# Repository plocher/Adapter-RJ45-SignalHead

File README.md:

# Adapter-RJ45-SignalHead
## License: CERN Open Hardware Licence v1.2

RJ45/8 breakout board, for driving signal heads from IOB-Signal

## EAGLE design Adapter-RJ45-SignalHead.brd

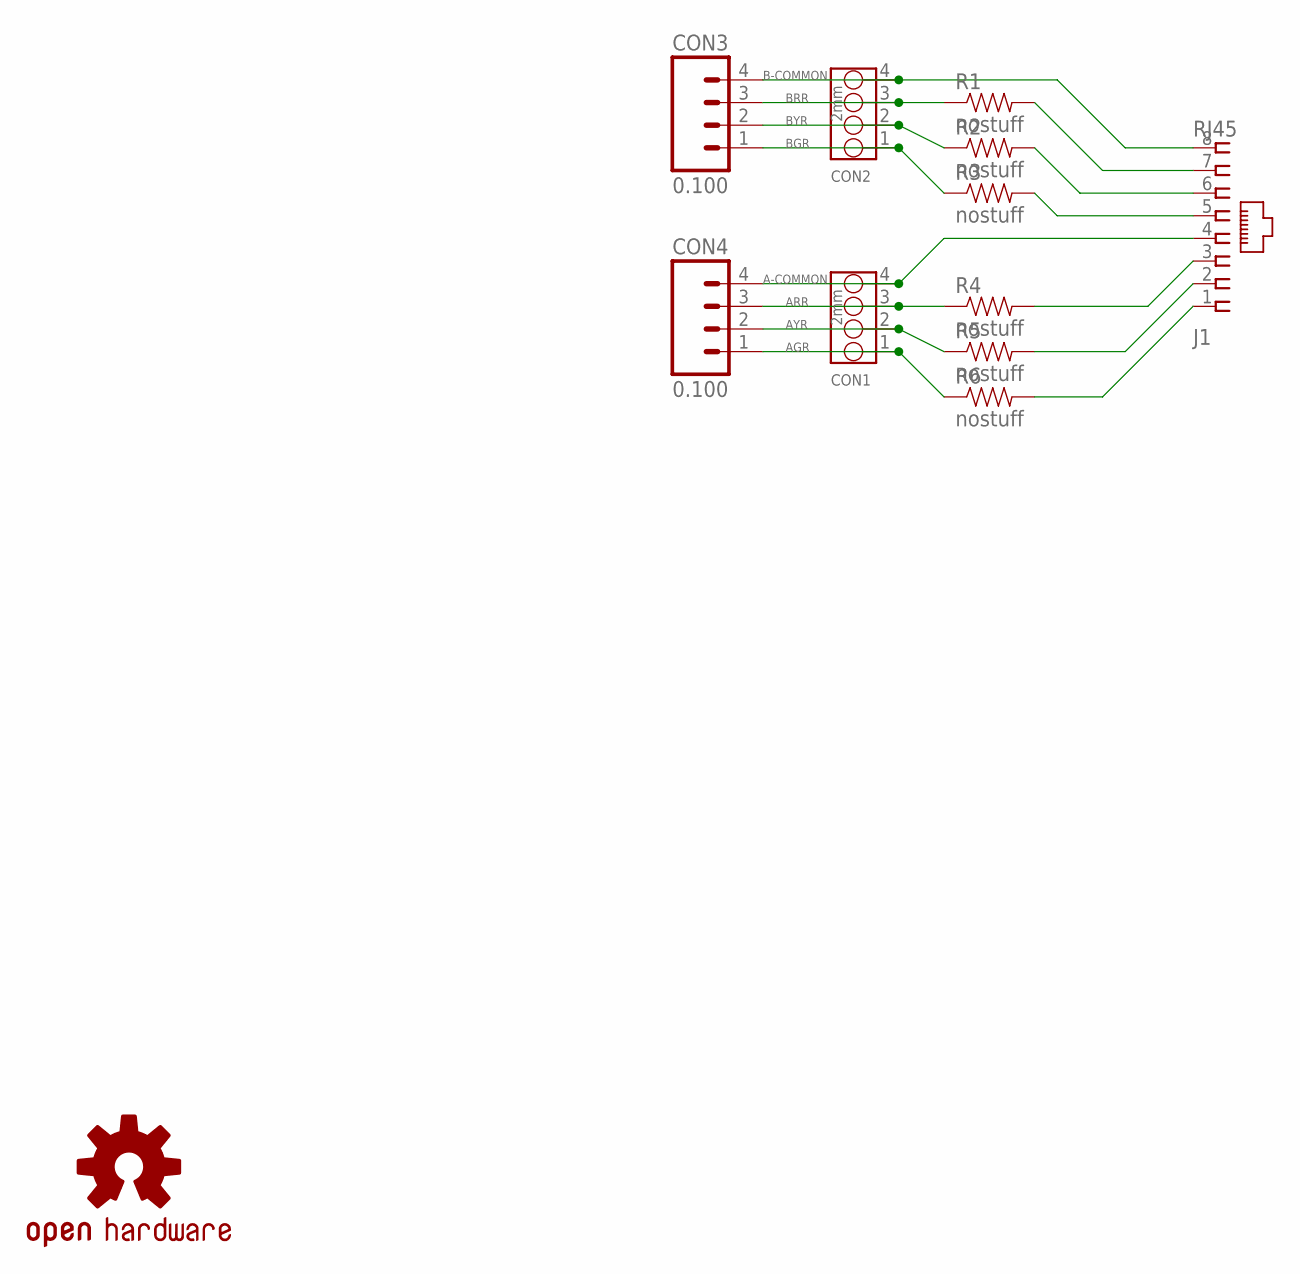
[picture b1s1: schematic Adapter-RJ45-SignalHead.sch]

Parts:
CON1, CON2: 2mm; 4P-2.0
CON3, CON4: 0.100; 1X04_LOCK
J1: RJ45; RJ45-NO-SHIELD
R1, R2, R3, R4, R5, R6: nostuff; CUT-R
U$1: OSHW; OSHW-LOGO-M

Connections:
A-COMMON: CON1.4, CON4.4, J1.4
AG: J1.1, R6.P1 (2)
AGR: CON1.1, CON4.1, R6.P2 (1)
AR: J1.3, R4.P1 (2)
ARR: CON1.3, CON4.3, R4.P2 (1)
AY: J1.2, R5.P1 (2)
AYR: CON1.2, CON4.2, R5.P2 (1)
B-COMMON: CON2.4, CON3.4, J1.8
BG: J1.5, R3.P1 (2)
BGR: CON2.1, CON3.1, R3.P2 (1)
BR: J1.7, R1.P1 (2)
BRR: CON2.3, CON3.3, R1.P2 (1)
BY: J1.6, R2.P1 (2)
BYR: CON2.2, CON3.2, R2.P2 (1)

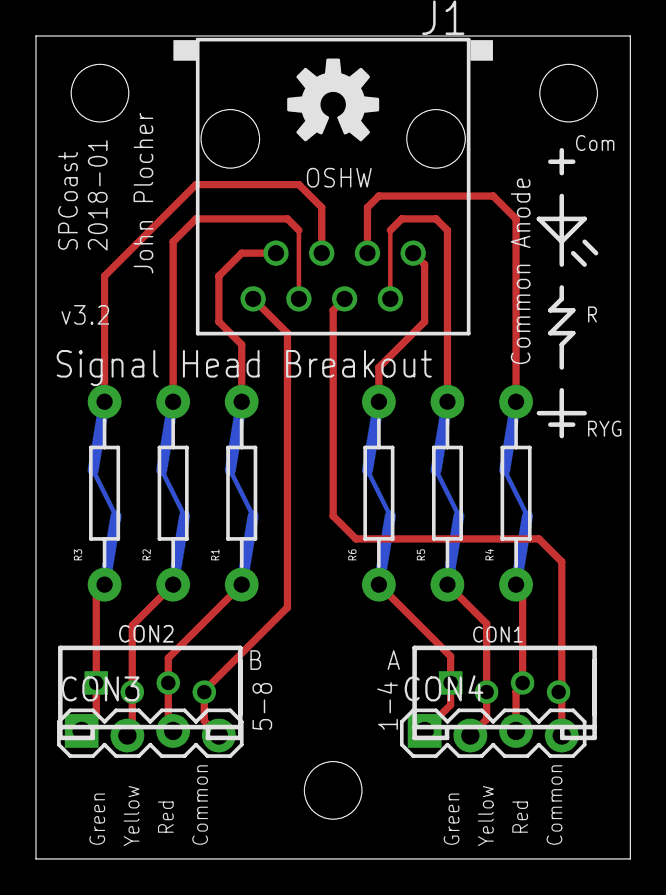
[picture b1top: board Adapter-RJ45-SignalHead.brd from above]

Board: 2 copper layers, 33.0 x 45.7 mm, 12 parts (0 on the bottom side), 14 nets.

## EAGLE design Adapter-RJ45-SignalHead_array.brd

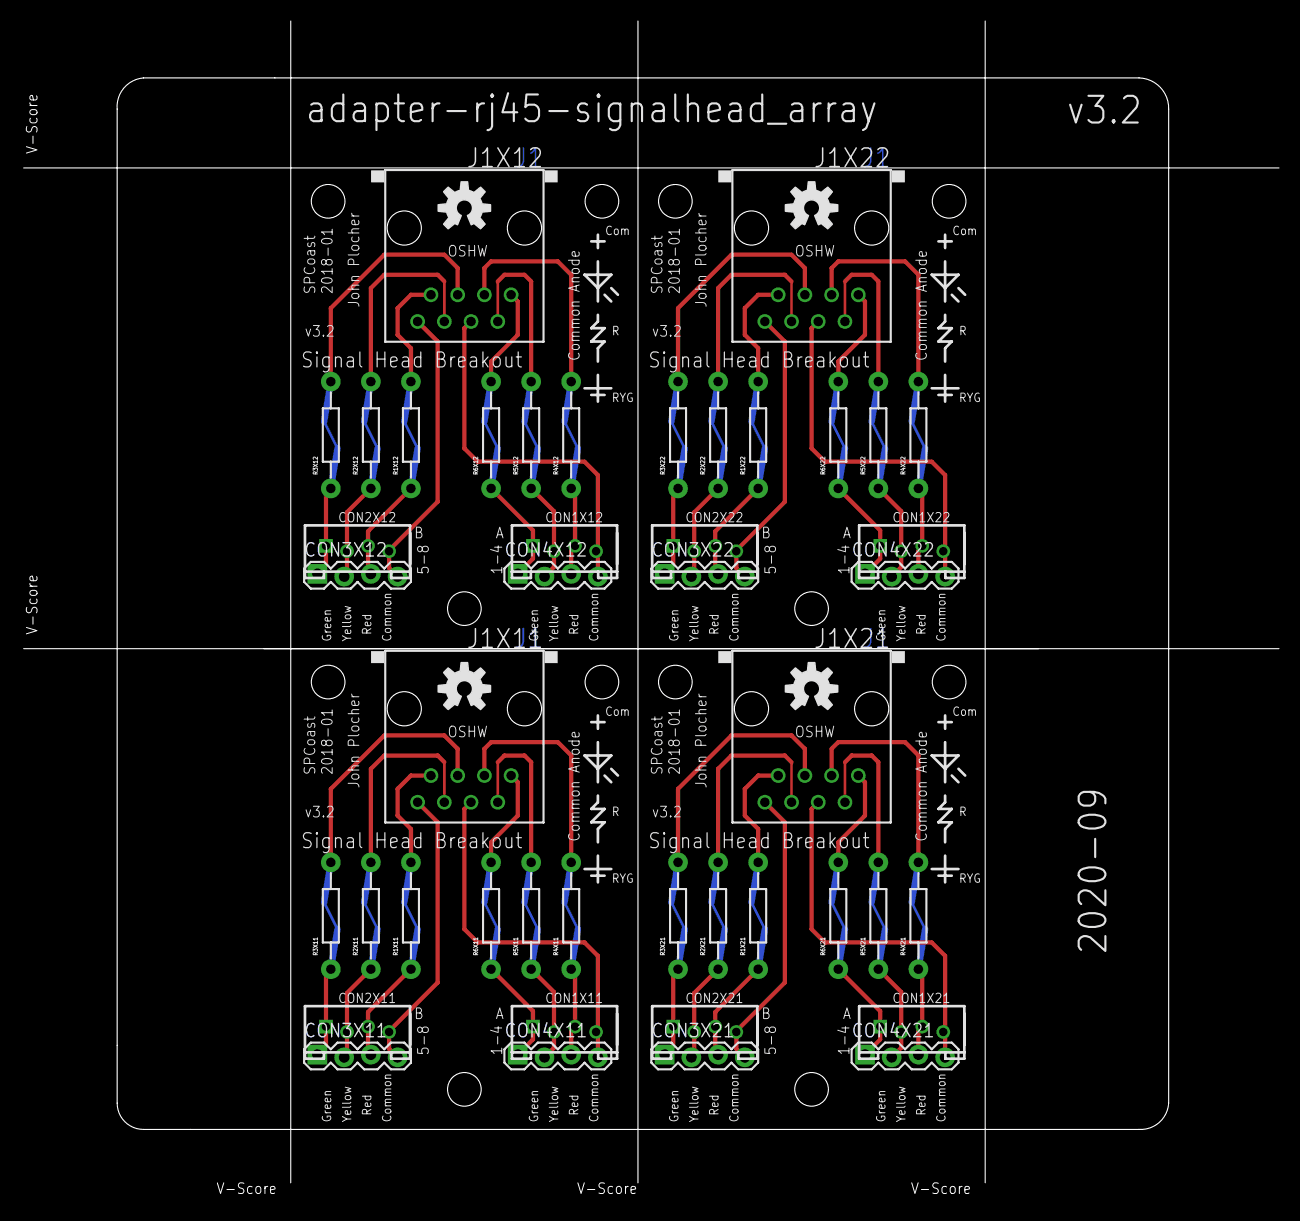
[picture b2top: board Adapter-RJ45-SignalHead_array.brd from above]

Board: 2 copper layers, 119.6 x 112.1 mm, 49 parts (0 on the bottom side), 56 nets.

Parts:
CON1X11, CON1X12, CON1X21, CON1X22, CON2X11, CON2X12, CON2X21, CON2X22: 2mm; 4P-2.0
CON3X11, CON3X12, CON3X21, CON3X22, CON4X11, CON4X12, CON4X21, CON4X22: 0.100; 1X04_LOCK
J1X11, J1X12, J1X21, J1X22: RJ45; RJ45-NO-SHIELD
R1X11, R1X12, R1X21, R1X22, R2X11, R2X12, R2X21, R2X22, R3X11, R3X12, R3X21, R3X22, R4X11, R4X12, R4X21, R4X22, R5X11, R5X12, R5X21, R5X22, R6X11, R6X12, R6X21, R6X22: nostuff; CUT-R
U$1X1: BOARD; BOARD-SEEED10X10-NOHOLES
U$1X11, U$1X12, U$1X21, U$1X22: OSHW; OSHW-LOGO-M

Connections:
A-COMMONX11: CON1X11.4, CON4X11.4, J1X11.4
A-COMMONX12: CON1X12.4, CON4X12.4, J1X12.4
A-COMMONX21: CON1X21.4, CON4X21.4, J1X21.4
A-COMMONX22: CON1X22.4, CON4X22.4, J1X22.4
AGRX11: CON1X11.1, CON4X11.1, R6X11.P2
AGRX12: CON1X12.1, CON4X12.1, R6X12.P2
AGRX21: CON1X21.1, CON4X21.1, R6X21.P2
AGRX22: CON1X22.1, CON4X22.1, R6X22.P2
AGX11: J1X11.1, R6X11.P1
AGX12: J1X12.1, R6X12.P1
AGX21: J1X21.1, R6X21.P1
AGX22: J1X22.1, R6X22.P1
ARRX11: CON1X11.3, CON4X11.3, R4X11.P2
ARRX12: CON1X12.3, CON4X12.3, R4X12.P2
ARRX21: CON1X21.3, CON4X21.3, R4X21.P2
ARRX22: CON1X22.3, CON4X22.3, R4X22.P2
ARX11: J1X11.3, R4X11.P1
ARX12: J1X12.3, R4X12.P1
ARX21: J1X21.3, R4X21.P1
ARX22: J1X22.3, R4X22.P1
AYRX11: CON1X11.2, CON4X11.2, R5X11.P2
AYRX12: CON1X12.2, CON4X12.2, R5X12.P2
AYRX21: CON1X21.2, CON4X21.2, R5X21.P2
AYRX22: CON1X22.2, CON4X22.2, R5X22.P2
AYX11: J1X11.2, R5X11.P1
AYX12: J1X12.2, R5X12.P1
AYX21: J1X21.2, R5X21.P1
AYX22: J1X22.2, R5X22.P1
B-COMMONX11: CON2X11.4, CON3X11.4, J1X11.8
B-COMMONX12: CON2X12.4, CON3X12.4, J1X12.8
B-COMMONX21: CON2X21.4, CON3X21.4, J1X21.8
B-COMMONX22: CON2X22.4, CON3X22.4, J1X22.8
BGRX11: CON2X11.1, CON3X11.1, R3X11.P2
BGRX12: CON2X12.1, CON3X12.1, R3X12.P2
BGRX21: CON2X21.1, CON3X21.1, R3X21.P2
BGRX22: CON2X22.1, CON3X22.1, R3X22.P2
BGX11: J1X11.5, R3X11.P1
BGX12: J1X12.5, R3X12.P1
BGX21: J1X21.5, R3X21.P1
BGX22: J1X22.5, R3X22.P1
BRRX11: CON2X11.3, CON3X11.3, R1X11.P2
BRRX12: CON2X12.3, CON3X12.3, R1X12.P2
BRRX21: CON2X21.3, CON3X21.3, R1X21.P2
BRRX22: CON2X22.3, CON3X22.3, R1X22.P2
BRX11: J1X11.7, R1X11.P1
BRX12: J1X12.7, R1X12.P1
BRX21: J1X21.7, R1X21.P1
BRX22: J1X22.7, R1X22.P1
BYRX11: CON2X11.2, CON3X11.2, R2X11.P2
BYRX12: CON2X12.2, CON3X12.2, R2X12.P2
BYRX21: CON2X21.2, CON3X21.2, R2X21.P2
BYRX22: CON2X22.2, CON3X22.2, R2X22.P2
BYX11: J1X11.6, R2X11.P1
BYX12: J1X12.6, R2X12.P1
BYX21: J1X21.6, R2X21.P1
BYX22: J1X22.6, R2X22.P1

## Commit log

2019-12-08 added graphic
2020-05-04 updated tags
2020-09-12 V3.2 - added CUT-R
2020-09-12 updated graphic
2020-09-17 typo in silkscreen
2020-10-05 added values for connectors
2020-10-06 normalized values

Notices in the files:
parts and their libraries:
SPCoast: http://freedomdefined.org/OSHW Creative Commons - Attribution - ShareAlike 3.0
